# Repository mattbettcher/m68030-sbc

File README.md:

# m68030-sbc

Homebrew MC68030 single-board computer.

See [68030-design/spec.md](68030-design/spec.md) for the design specification.

Open [68030-design/kicad/m68030-sbc.kicad_pro](68030-design/kicad/m68030-sbc.kicad_pro) in KiCad 9.

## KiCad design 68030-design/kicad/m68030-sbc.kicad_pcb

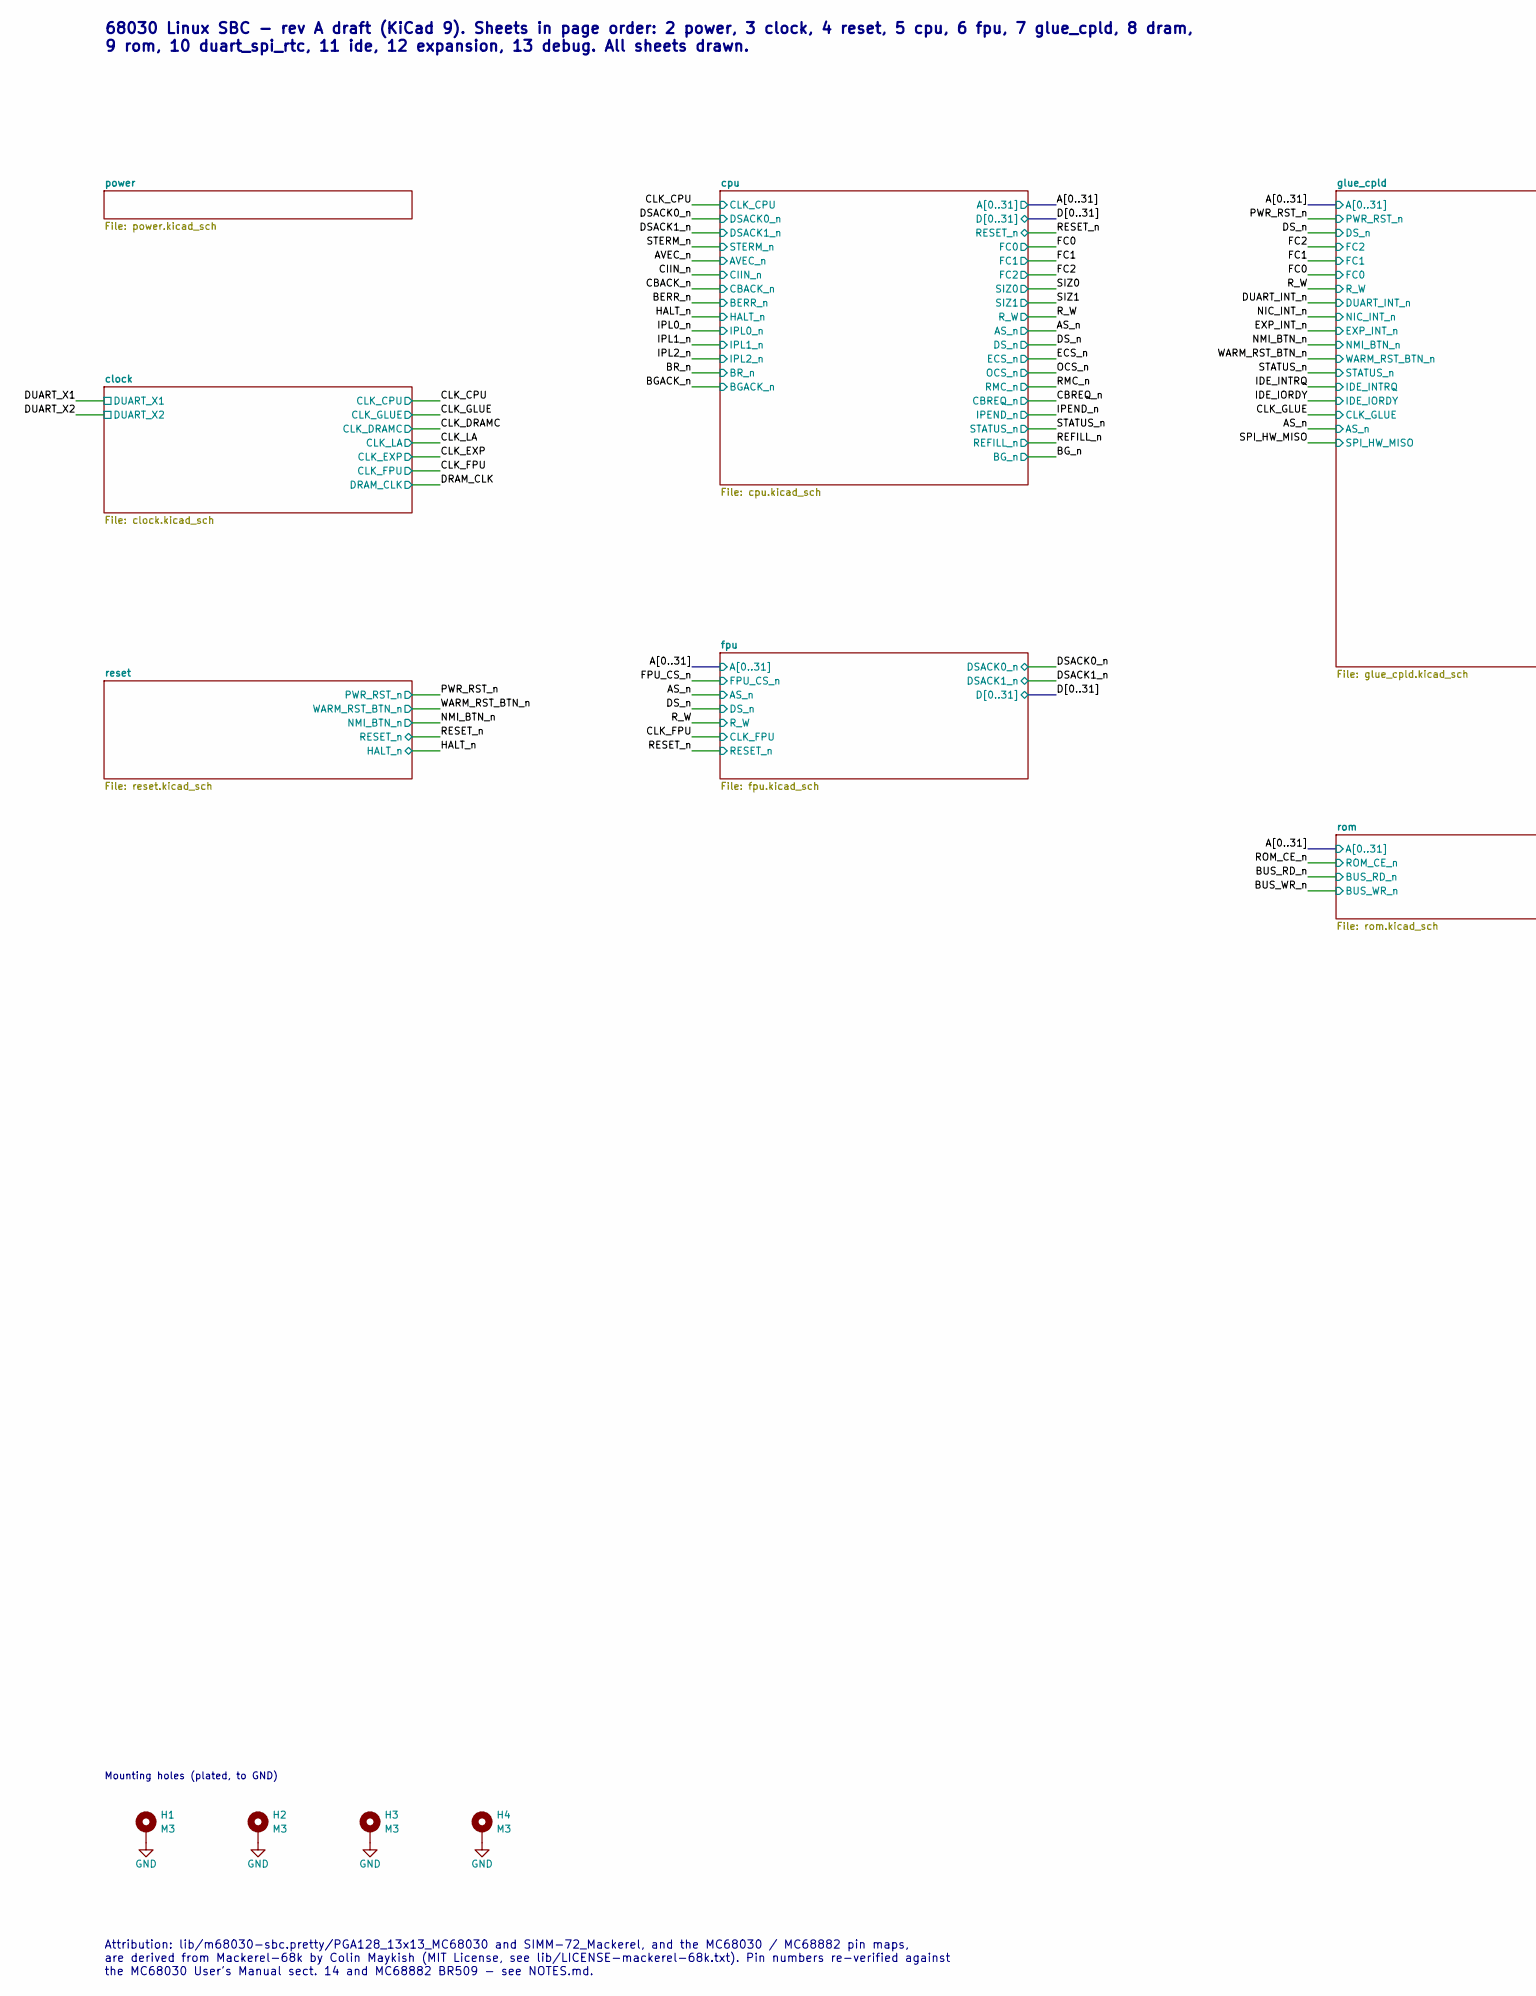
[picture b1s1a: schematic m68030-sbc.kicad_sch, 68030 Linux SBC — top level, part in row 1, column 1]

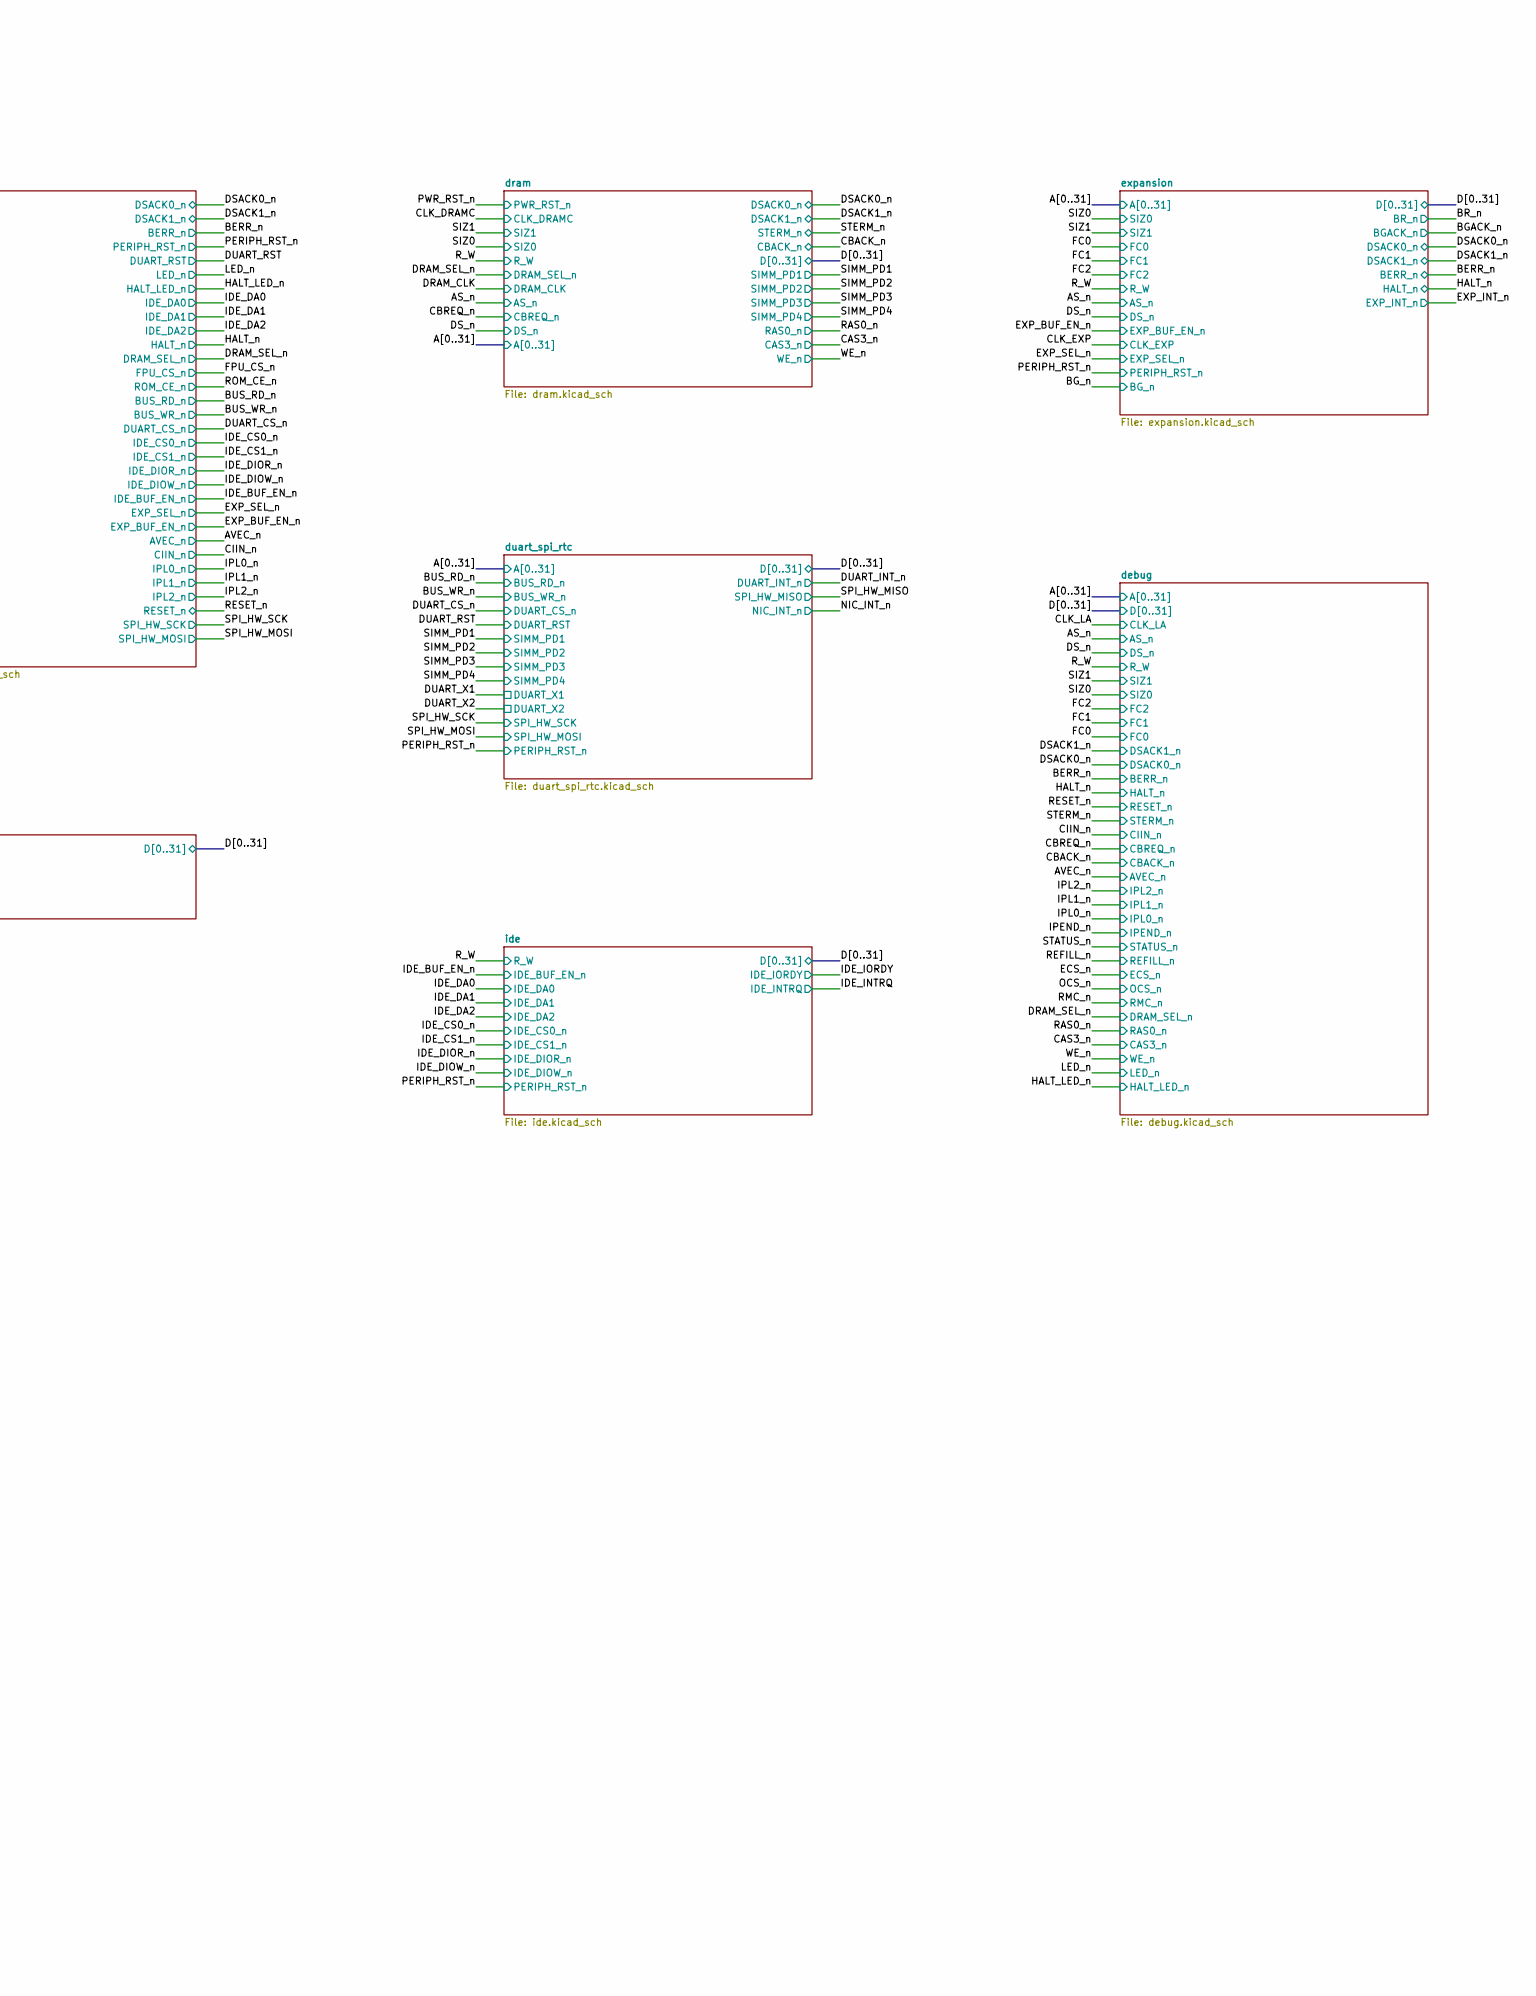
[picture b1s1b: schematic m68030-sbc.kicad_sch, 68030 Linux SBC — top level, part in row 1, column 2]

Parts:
H1, H2, H3, H4: M3; MountingHole_3.2mm_M3_Pad

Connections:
GND: H1.1, H2.1, H3.1, H4.1; also elsewhere on the board

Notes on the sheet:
68030 Linux SBC - rev A draft (KiCad 9). Sheets in page order: 2 power, 3 clock, 4 reset, 5 cpu, 6 fpu, 7 glue_cpld, 8 dram, 9 rom, 10 duart_spi_rtc, 11 ide, 12 expansion, 13 debug. All sheets drawn.
Attribution: lib/m68030-sbc.pretty/PGA128_13x13_MC68030 and SIMM-72_Mackerel, and the MC68030 / MC68882 pin maps, are derived from Mackerel-68k by Colin Maykish (MIT License, see lib/LICENSE-mackerel-68k.txt). Pin numbers re-verified against the MC68030 User's Manual sect. 14 and MC68882 BR509 - se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
Mounting holes (plated, to GND)

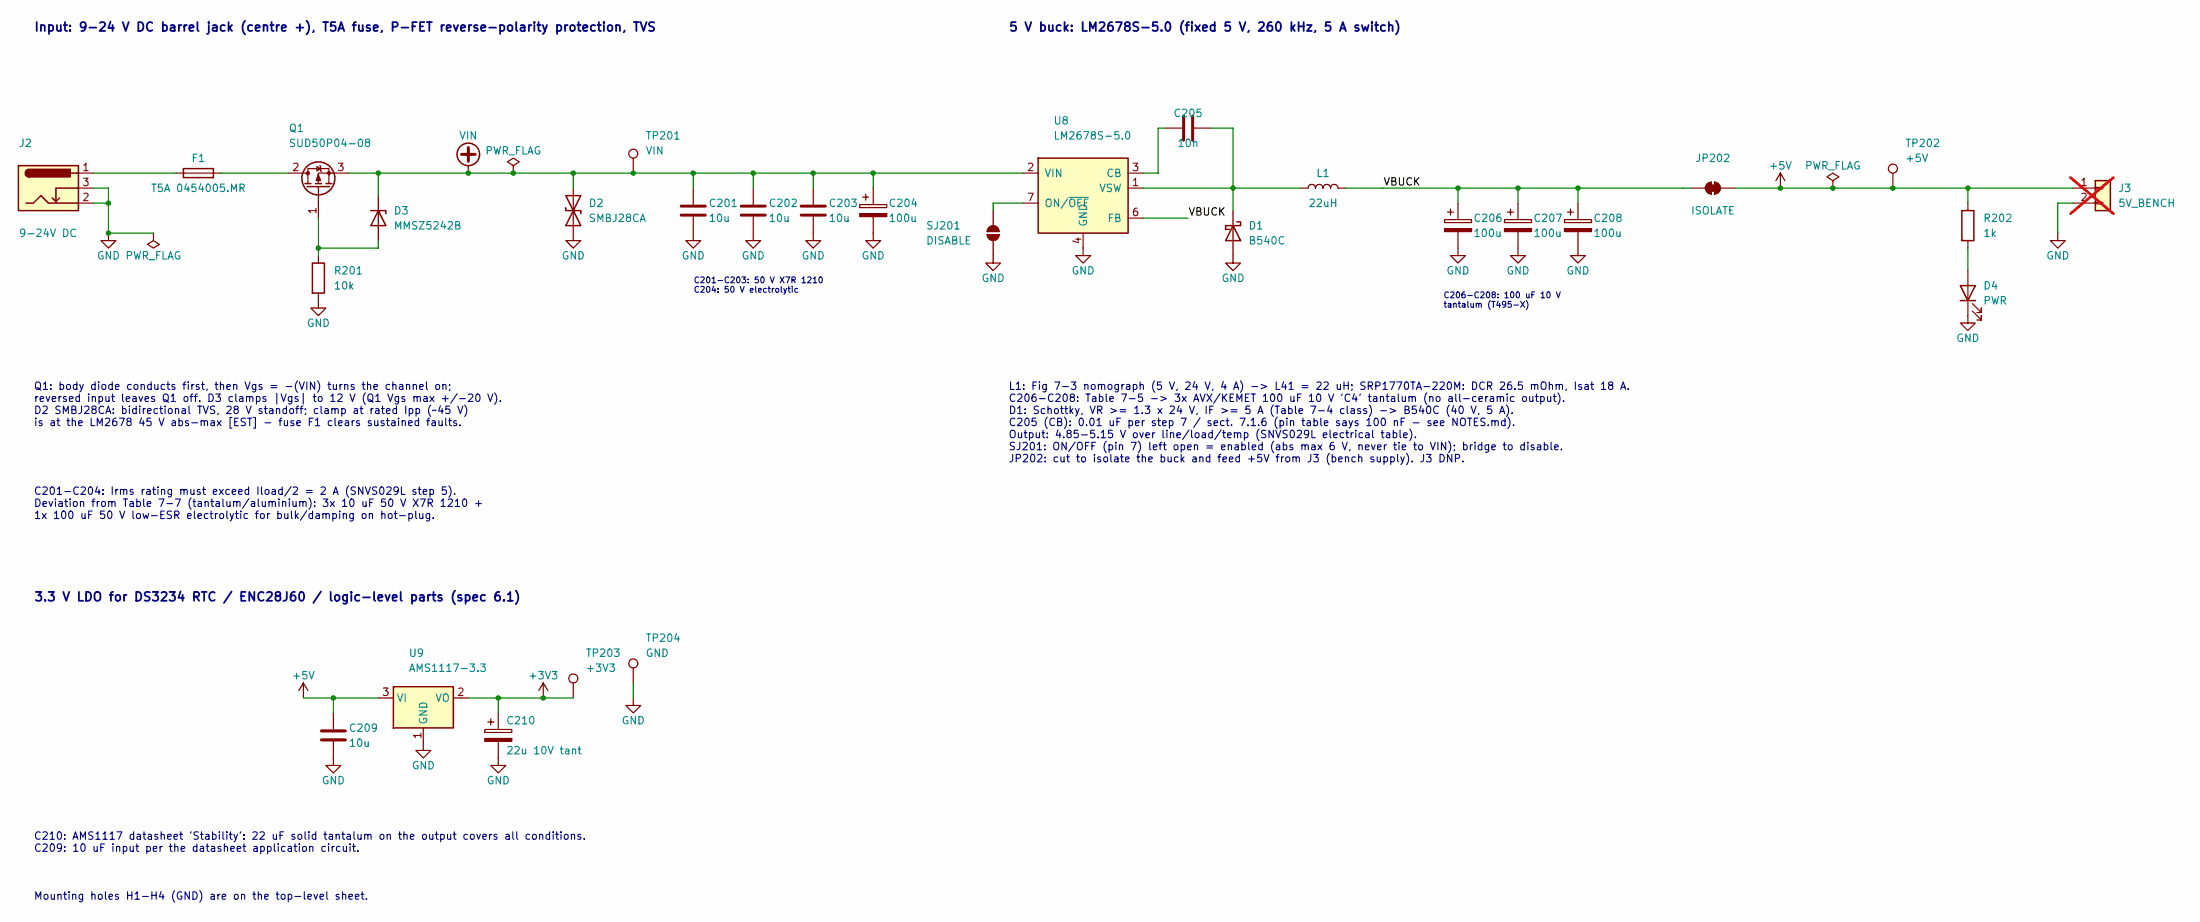
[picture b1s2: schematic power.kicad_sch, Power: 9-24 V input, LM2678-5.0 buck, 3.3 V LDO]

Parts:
C201, C202, C203: 10u; C_1210_3225Metric; Rating 10 uF 50 V X7R 1210
C204: 100u; CP_Elec_10x10.5; Rating 100 uF 50 V low-ESR aluminium, 10x10.5
C205: 10n; C_0603_1608Metric
C206, C207, C208: 100u; CP_EIA-7343-43_Kemet-X; Rating 100 uF 10 V tantalum; MPN KEMET T495X107K010ATE100 [VERIFY]
C209: 10u; C_1206_3216Metric
C210: 22u 10V tant; CP_EIA-3528-21_Kemet-B
D1: B540C; D_SMC; MPN B540C-13-F
D2: SMBJ28CA; D_SMB; MPN SMBJ28CA (28 V standoff, bidirectional)
D3: MMSZ5242B; D_SOD-123; MPN MMSZ5242B (12 V)
D4: PWR; LED_0805_2012Metric
F1: T5A 0454005.MR; Fuse_Littelfuse-NANO2-451_453; MPN Littelfuse 0454005.MR
J2: 9-24V DC; BarrelJack_Horizontal
J3: 5V_BENCH; PinHeader_1x02_P2.54mm_Vertical; not fitted
JP202: ISOLATE; SolderJumper-2_P1.3mm_Bridged_RoundedPad1.0x1.5mm
L1: 22uH; L_Bourns_SRP1770TA_16.9x16.9mm; MPN Bourns SRP1770TA-220M
Q1: SUD50P04-08; TO-252-2; MPN SUD50P04-08-GE3
R201: 10k; R_0603_1608Metric
R202: 1k; R_0603_1608Metric
SJ201: DISABLE; SolderJumper-2_P1.3mm_Open_RoundedPad1.0x1.5mm
TP201: VIN; TestPoint_Pad_D1.5mm
TP202: +5V; TestPoint_Pad_D1.5mm
TP203: +3V3; TestPoint_Pad_D1.5mm
TP204: GND; TestPoint_Pad_D1.5mm
U8: LM2678S-5.0; TO-263-7_TabPin4; MPN LM2678S-5.0/NOPB
U9: AMS1117-3.3; SOT-223-3_TabPin2; MPN AMS1117-3.3

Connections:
+3V3: C210.1, TP203.1, U9.2 (VO); also elsewhere on the board
+5V: C209.1, J3.1, JP202.2 (B), R202.1, TP202.1, U9.3 (VI); also elsewhere on the board
/power/VBUCK: C206.1, C207.1, C208.1, JP202.1 (A), L1.2, U8.6 (FB)
GND: C201.2, C202.2, C203.2, C204.2, C206.2, C207.2, C208.2, C209.2, C210.2, D1.2 (A), D2.1 (A1), D4.1 (K), J2.2, J2.3, J3.2, R201.2, SJ201.1 (A), TP204.1, U8.4 (GND), U9.1 (GND); also elsewhere on the board
unnamed: C205.2, D1.1 (K), L1.1, U8.1 (VSW)
unnamed: D3.2 (A), Q1.1 (G), R201.1
unnamed: D4.2 (A), R202.2
unnamed: F1.1, J2.1
unnamed: F1.2, Q1.2 (D)
unnamed: SJ201.2 (B), U8.7 (ON/~OFF)
unnamed: C205.1, U8.3 (CB)
VIN: C201.1, C202.1, C203.1, C204.1, D2.2 (A2), D3.1 (K), Q1.3 (S), TP201.1, U8.2 (VIN)

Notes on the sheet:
Input: 9-24 V DC barrel jack (centre +), T5A fuse, P-FET reverse-polarity protection, TVS
C201-C203: 50 V X7R 1210 C204: 50 V electrolytic
Q1: body diode conducts first, then Vgs = -(VIN) turns the channel on; reversed input leaves Q1 off. D3 clamps |Vgs| to 12 V (Q1 Vgs max +/-20 V). D2 SMBJ28CA: bidirectional TVS, 28 V standoff; clamp at rated Ipp (~45 V) is at the LM2678 45 V abs-max [EST] - fuse F1 clears sustained faults.
C201-C204: Irms rating must exceed Iload/2 = 2 A (SNVS029L step 5). Deviation from Table 7-7 (tantalum/aluminium): 3x 10 uF 50 V X7R 1210 + 1x 100 uF 50 V low-ESR electrolytic for bulk/damping on hot-plug.
5 V buck: LM2678S-5.0 (fixed 5 V, 260 kHz, 5 A switch)
C206-C208: 100 uF 10 V tantalum (T495-X)
L1: Fig 7-3 nomograph (5 V, 24 V, 4 A) -> L41 = 22 uH; SRP1770TA-220M: DCR 26.5 mOhm, Isat 18 A. C206-C208: Table 7-5 -> 3x AVX/KEMET 100 uF 10 V 'C4' tantalum (no all-ceramic output). D1: Schottky, VR >= 1.3 x 24 V, IF >= 5 A (Table 7-4 class) -> B540C (40 V, 5 A). C205 (CB): 0.01 uF per step 7 / 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
3.3 V LDO for DS3234 RTC / ENC28J60 / logic-level parts (spec 6.1)
C210: AMS1117 datasheet 'Stability': 22 uF solid tantalum on the output covers all conditions. C209: 10 uF input per the datasheet application circuit.
Mounting holes H1-H4 (GND) are on the top-level sheet.

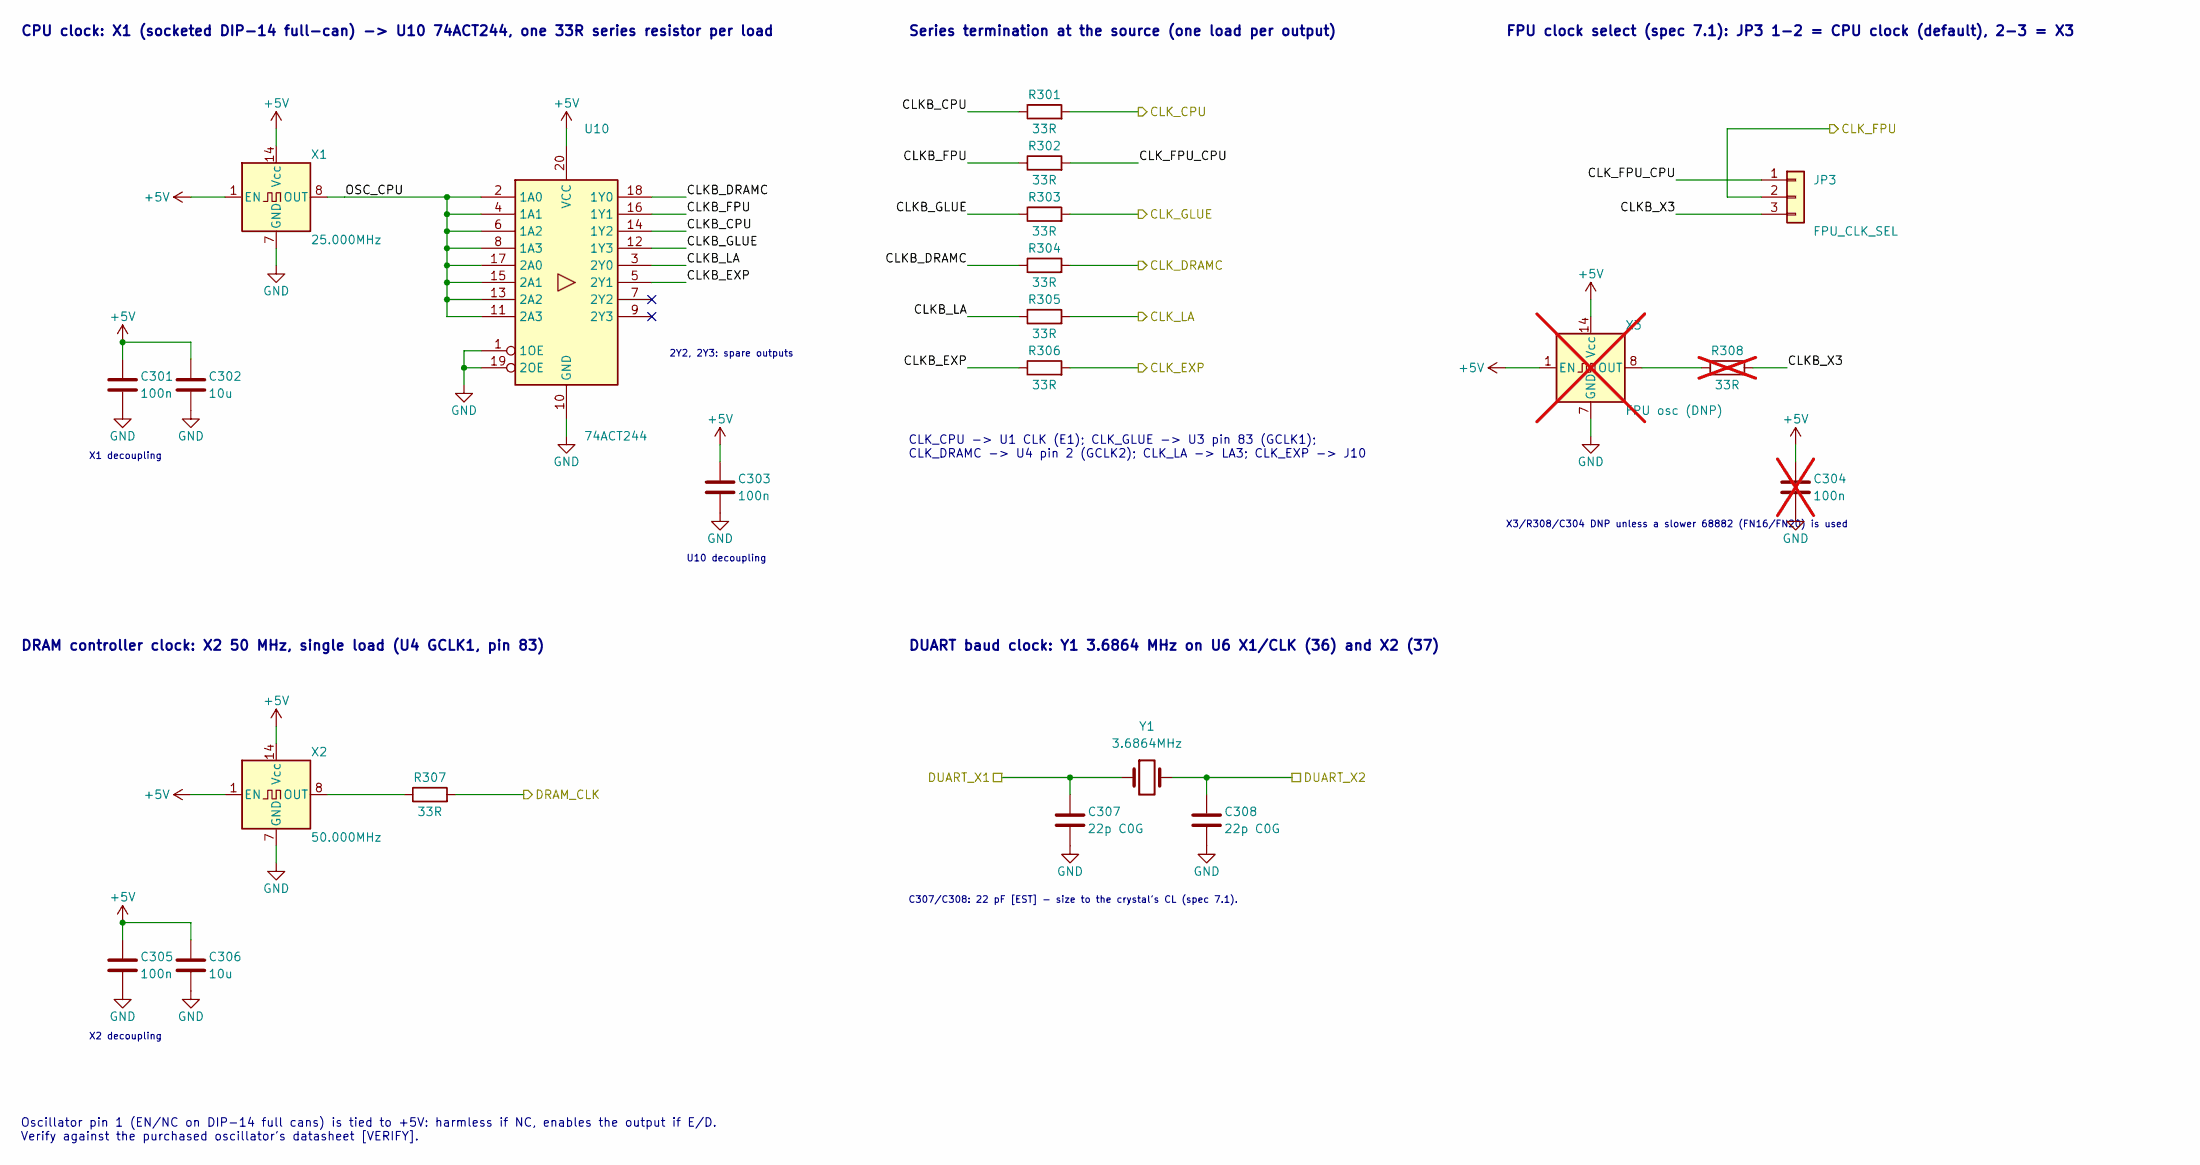
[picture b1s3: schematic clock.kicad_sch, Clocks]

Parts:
C301, C303, C305: 100n; C_0603_1608Metric
C302, C306: 10u; C_1206_3216Metric
C304: 100n; C_0603_1608Metric; not fitted
C307, C308: 22p C0G; C_0603_1608Metric
JP3: FPU_CLK_SEL; PinHeader_1x03_P2.54mm_Vertical
R301, R302, R303, R304, R305, R306, R307: 33R; R_0603_1608Metric
R308: 33R; R_0603_1608Metric; not fitted
U10: 74ACT244; SOIC-20W_7.5x12.8mm_P1.27mm; MPN SN74ACT244DWR
X1: 25.000MHz; Oscillator_SMD_ECS-3951M_7.0x5.0mm_DIP14PinMap; MPN ECS-3951M-250-BN-TR
X2: 50.000MHz; Oscillator_SMD_ECS-3951M_7.0x5.0mm_DIP14PinMap; MPN ECS-3951M-500-BN-TR
X3: FPU osc (DNP); Oscillator_SMD_ECS-3951M_7.0x5.0mm_DIP14PinMap; MPN ECS-3951M-200-BN-TR [VERIFY freq vs 688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; not fitted
Y1: 3.6864MHz; Crystal_HC49-4H_Vertical; MPN 3.6864 MHz HC-49 (CL per chosen part)

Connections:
+5V: C301.1, C302.1, C303.1, C304.1, C305.1, C306.1, U10.20 (VCC), X1.1 (EN), X1.14 (Vcc), X2.1 (EN), X2.14 (Vcc), X3.1 (EN), X3.14 (Vcc); also elsewhere on the board
/CLK_CPU: R301.2; also elsewhere on the board
/CLK_DRAMC: R304.2; also elsewhere on the board
/CLK_EXP: R306.2; also elsewhere on the board
/CLK_FPU: JP3.2; also elsewhere on the board
/CLK_GLUE: R303.2; also elsewhere on the board
/CLK_LA: R305.2; also elsewhere on the board
/DRAM_CLK: R307.2; also elsewhere on the board
/DUART_X1: C307.1, Y1.1; also elsewhere on the board
/DUART_X2: C308.1, Y1.2; also elsewhere on the board
/clock/CLKB_CPU: R301.1, U10.14 (1Y2)
/clock/CLKB_DRAMC: R304.1, U10.18 (1Y0)
/clock/CLKB_EXP: R306.1, U10.5 (2Y1)
/clock/CLKB_FPU: R302.1, U10.16 (1Y1)
/clock/CLKB_GLUE: R303.1, U10.12 (1Y3)
/clock/CLKB_LA: R305.1, U10.3 (2Y0)
/clock/CLKB_X3: JP3.3, R308.2
/clock/CLK_FPU_CPU: JP3.1, R302.2
/clock/OSC_CPU: U10.2 (1A0), U10.4 (1A1), U10.6 (1A2), U10.8 (1A3), U10.11 (2A3), U10.13 (2A2), U10.15 (2A1), U10.17 (2A0), X1.8 (OUT)
GND: C301.2, C302.2, C303.2, C304.2, C305.2, C306.2, C307.2, C308.2, U10.1 (1OE), U10.10 (GND), U10.19 (2OE), X1.7 (GND), X2.7 (GND), X3.7 (GND); also elsewhere on the board
unnamed: R307.1, X2.8 (OUT)
unnamed: R308.1, X3.8 (OUT)

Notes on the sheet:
CPU clock: X1 (socketed DIP-14 full-can) -> U10 74ACT244, one 33R series resistor per load
2Y2, 2Y3: spare outputs
X1 decoupling
U10 decoupling
Series termination at the source (one load per output)
CLK_CPU -> U1 CLK (E1); CLK_GLUE -> U3 pin 83 (GCLK1); CLK_DRAMC -> U4 pin 2 (GCLK2); CLK_LA -> LA3; CLK_EXP -> J10
FPU clock select (spec 7.1): JP3 1-2 = CPU clock (default), 2-3 = X3
X3/R308/C304 DNP unless a slower 68882 (FN16/FN20) is used
DRAM controller clock: X2 50 MHz, single load (U4 GCLK1, pin 83)
X2 decoupling
DUART baud clock: Y1 3.6864 MHz on U6 X1/CLK (36) and X2 (37)
C307/C308: 22 pF [EST] - size to the crystal's CL (spec 7.1).
Oscillator pin 1 (EN/NC on DIP-14 full cans) is tied to +5V: harmless if NC, enables the output if E/D. Verify against the purchased oscillator's datasheet [VERIFY].

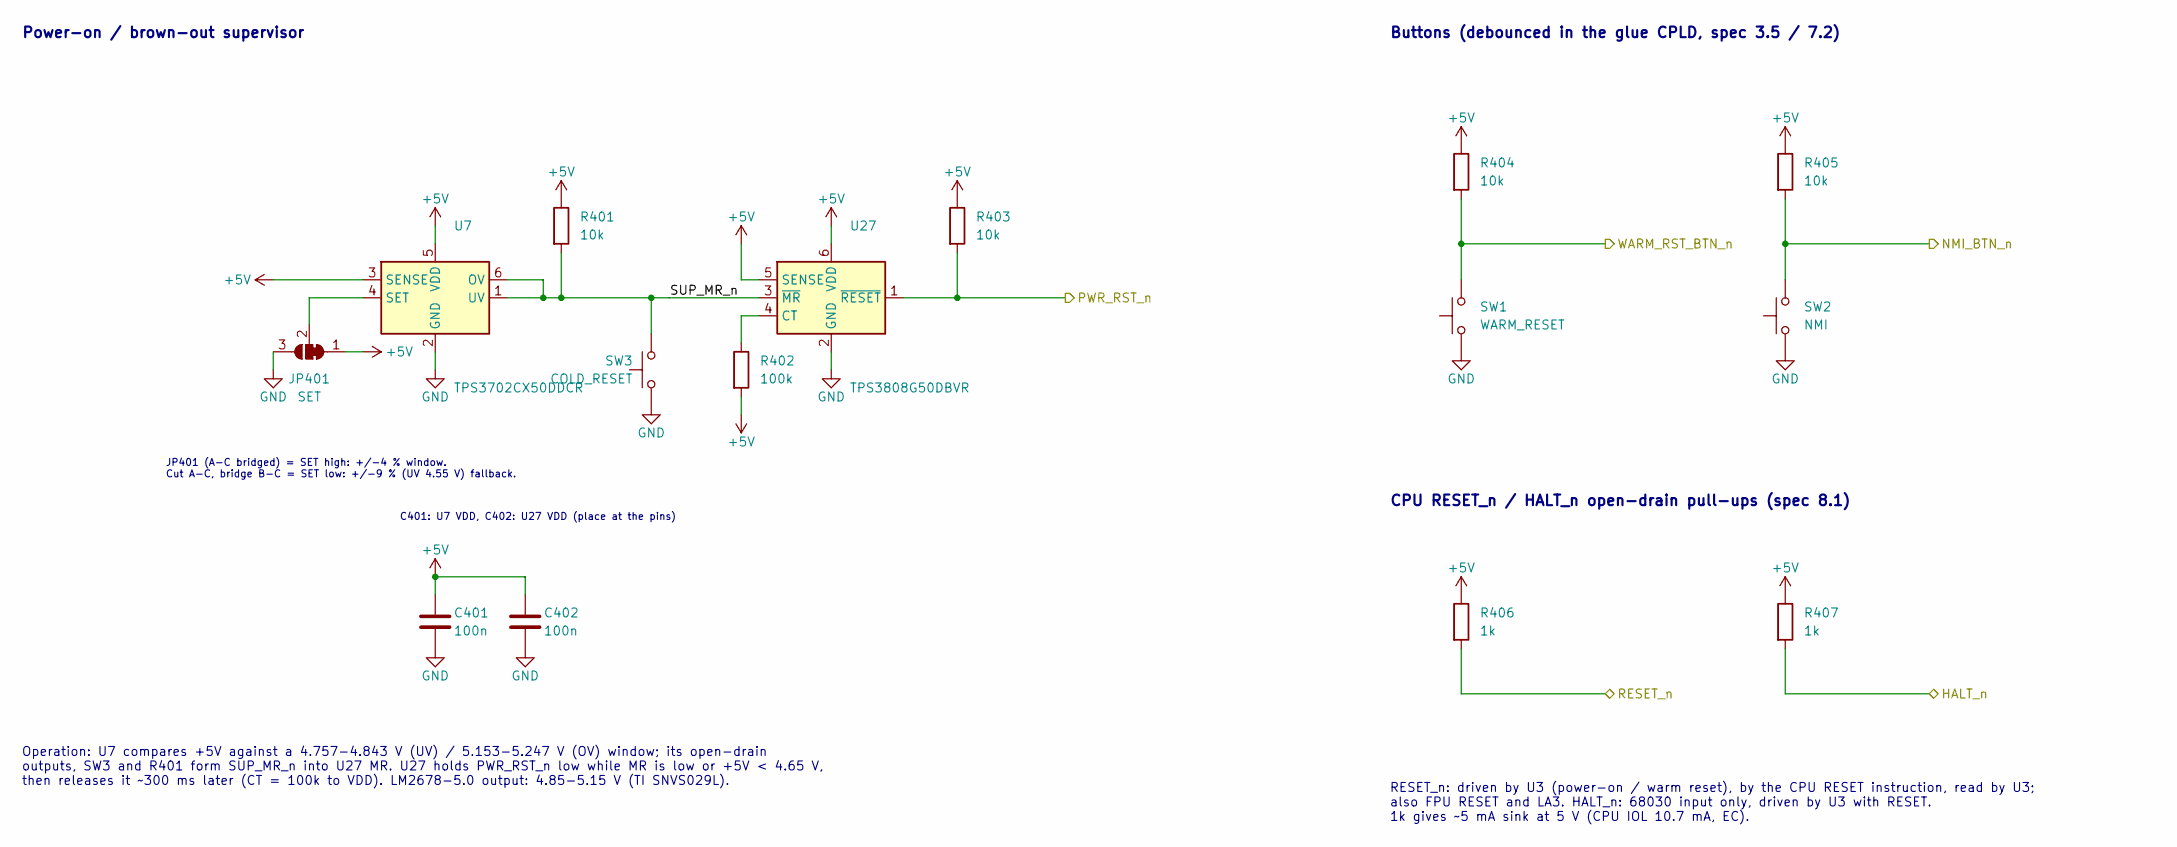
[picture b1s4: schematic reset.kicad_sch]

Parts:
C401, C402: 100n; C_0603_1608Metric
JP401: SET; SolderJumper-3_P1.3mm_Bridged12_RoundedPad1.0x1.5mm
R401, R403, R404, R405: 10k; R_0603_1608Metric
R402: 100k; R_0603_1608Metric
R406, R407: 1k; R_0603_1608Metric
SW1: WARM_RESET; SW_PUSH_6mm_H5mm
SW2: NMI; SW_PUSH_6mm_H5mm
SW3: COLD_RESET; SW_PUSH_6mm_H5mm
U7: TPS3702CX50DDCR; SOT-23-6; MPN TPS3702CX50DDCR
U27: TPS3808G50DBVR; SOT-23-6; MPN TPS3808G50DBVR

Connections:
+5V: C401.1, C402.1, JP401.1 (A), R401.1, R402.2, R403.1, R404.1, R405.1, R406.1, R407.1, U7.3 (SENSE), U7.5 (VDD), U27.5 (SENSE), U27.6 (VDD); also elsewhere on the board
/HALT_n: R407.2; also elsewhere on the board
/NMI_BTN_n: R405.2, SW2.2; also elsewhere on the board
/PWR_RST_n: R403.2, U27.1 (~RESET); also elsewhere on the board
/RESET_n: R406.2; also elsewhere on the board
/WARM_RST_BTN_n: R404.2, SW1.2; also elsewhere on the board
/reset/SUP_MR_n: R401.2, SW3.2, U7.1 (UV), U7.6 (OV), U27.3 (~MR)
GND: C401.2, C402.2, JP401.3 (B), SW1.1, SW2.1, SW3.1, U7.2 (GND), U27.2 (GND); also elsewhere on the board
unnamed: JP401.2 (C), U7.4 (SET)
unnamed: R402.1, U27.4 (CT)

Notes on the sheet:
Power-on / brown-out supervisor
JP401 (A-C bridged) = SET high: +/-4 % window. Cut A-C, bridge B-C = SET low: +/-9 % (UV 4.55 V) fallback.
C401: U7 VDD, C402: U27 VDD (place at the pins)
Operation: U7 compares +5V against a 4.757-4.843 V (UV) / 5.153-5.247 V (OV) window; its open-drain outputs, SW3 and R401 form SUP_MR_n into U27 MR. U27 holds PWR_RST_n low while MR is low or +5V < 4.65 V, then releases it ~300 ms later (CT = 100k to VDD). LM2678-5.0 output: 4.85-5.15 V (TI SNVS029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
Buttons (debounced in the glue CPLD, spec 3.5 / 7.2)
CPU RESET_n / HALT_n open-drain pull-ups (spec 8.1)
RESET_n: driven by U3 (power-on / warm reset), by the CPU RESET instruction, read by U3; also FPU RESET and LA3. HALT_n: 68030 input only, driven by U3 with RESET. 1k gives ~5 mA sink at 5 V (CPU IOL 10.7 mA, EC).
